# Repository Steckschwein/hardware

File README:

# Homebrew 8bit computer based on 65c02 CPU #

## Description ##
We are developing a retro style 8bit computer based on the 65c02 CPU. 

## Features ##
65c02 CPU @ 8MHz
TMS9929 Video Display Controller
Yamaha YM3812 (OPL2) Sound
rs232 serial interface using UART 16550
SD Card Interface

[Steckschwein Web Site](http://steckschwein.de/)

The goal is to design a machine that could have existed back in the home computer era, but with "modern" interfaces like PS/2, full fledged rs232, SPI, etc. 

We use as much open source tools as possible, such as 
ACME Cross Assembler
cc65
make
Mercurial
galasm
KiCAD
avr-gcc

The repository contains the assembler source for the system firmware, test and demo programs, galasm source for the address decoder and the KiCAD project files for schematics and layout.

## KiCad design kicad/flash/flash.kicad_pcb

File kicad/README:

the current steckschwein revision consists of three boards found in the directories
cpu_mem_rdy
io_uart
V9958_OPL2

everything else is kept for historical and sentimental reasons.

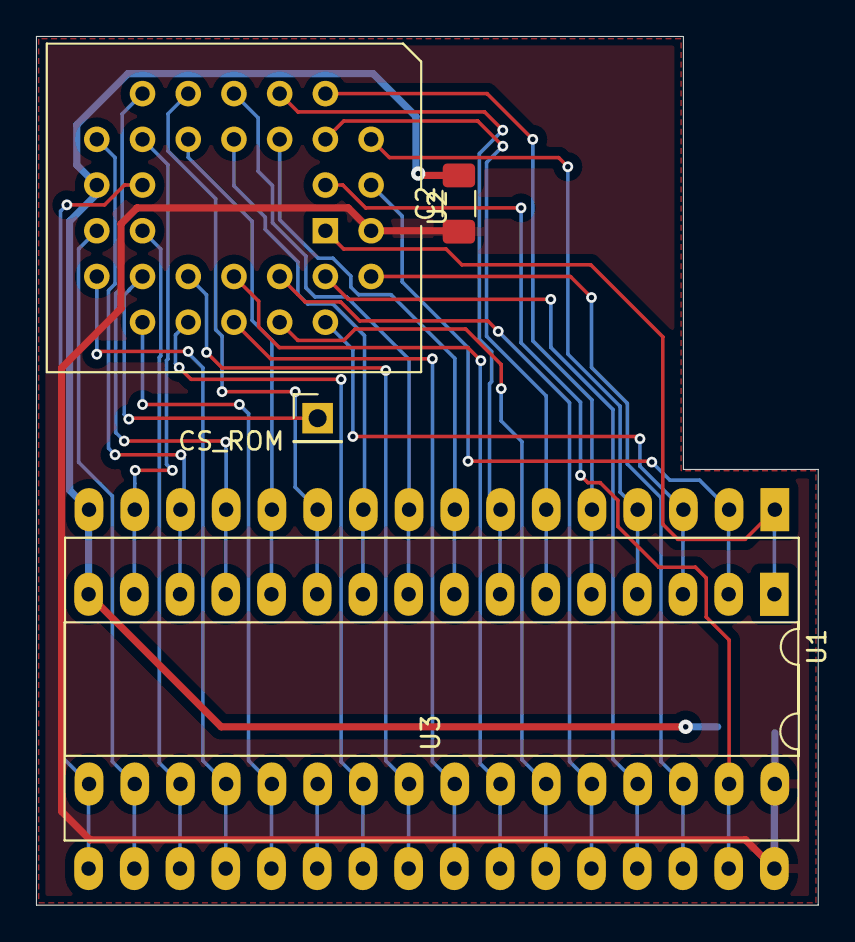
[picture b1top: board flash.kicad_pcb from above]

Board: 4 copper layers, 43.4 x 48.3 mm, 6 parts (1 on the bottom side), 33 nets.

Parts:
C1, C2: C; C_1206_3216Metric_Pad1.33x1.80mm_HandSolder
CS_ROM: Conn_01x01_Pin; PinHeader_1x01_P2.54mm_Vertical
U1, U3: AS6C4008-55PCN; DIP-32_W15.24mm_LongPads
U2: SST39SF040; PLCC-32_THT-Socket

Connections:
/A0: U1.12 (A0), U2.12 (A0), U3.12 (A0)
/A1: U1.11 (A1), U2.11 (A1), U3.11 (A1)
/A2: U1.10 (A2), U2.10 (A2), U3.10 (A2)
/A3: U1.9 (A3), U2.9 (A3), U3.9 (A3)
/A4: U1.8 (A4), U2.8 (A4), U3.8 (A4)
/A5: U1.7 (A5), U2.7 (A5), U3.7 (A5)
/A6: U1.6 (A6), U2.6 (A6), U3.6 (A6)
/A7: U1.5 (A7), U2.5 (A7), U3.5 (A7)
/A8: U1.27 (A8), U2.27 (A8), U3.27 (A8)
/A9: U1.26 (A9), U2.26 (A9), U3.26 (A9)
/A10: U1.23 (A10), U2.23 (A10), U3.23 (A10)
/A11: U1.25 (A11), U2.25 (A11), U3.25 (A11)
/A12: U1.4 (A12), U2.4 (A12), U3.4 (A12)
/A13: U1.28 (A13), U2.28 (A13), U3.28 (A13)
/A14: U1.3 (A14), U2.29 (A14), U3.3 (A14)
/A15: U1.31 (A15), U2.3 (A15), U3.31 (A15)
/A16: U1.2 (A16), U2.2 (A16), U3.2 (A16)
/A17: U1.30 (A17), U2.30 (A17), U3.30 (A17)
/A18: U1.1 (A18), U2.1 (A18), U3.1 (A18)
/D0: U1.13 (DQ0), U2.13 (D0), U3.13 (DQ0)
/D1: U1.14 (DQ1), U2.14 (D1), U3.14 (DQ1)
/D2: U1.15 (DQ2), U2.15 (D2), U3.15 (DQ2)
/D3: U1.17 (DQ3), U2.17 (D3), U3.17 (DQ3)
/D4: U1.18 (DQ4), U2.18 (D4), U3.18 (DQ4)
/D5: U1.19 (DQ5), U2.19 (D5), U3.19 (DQ5)
/D6: U1.20 (DQ6), U2.20 (D6), U3.20 (DQ6)
/D7: U1.21 (DQ7), U2.21 (D7), U3.21 (DQ7)
/~CE: U1.22 (CE#), U3.22 (CE#)
/~CS_ROM: CS_ROM.1, U2.22 (CE)
/~OE: U1.24 (OE#), U2.24 (OE), U3.24 (OE#)
/~WE: U1.29 (WE#), U2.31 (PGM), U3.29 (WE#)
GND: C1.2, C2.2, U1.16 (VSS), U2.16 (GND), U3.16 (VSS)
VCC: C1.1, C2.1, U1.32 (VCC), U2.32 (VCC), U3.32 (VCC)

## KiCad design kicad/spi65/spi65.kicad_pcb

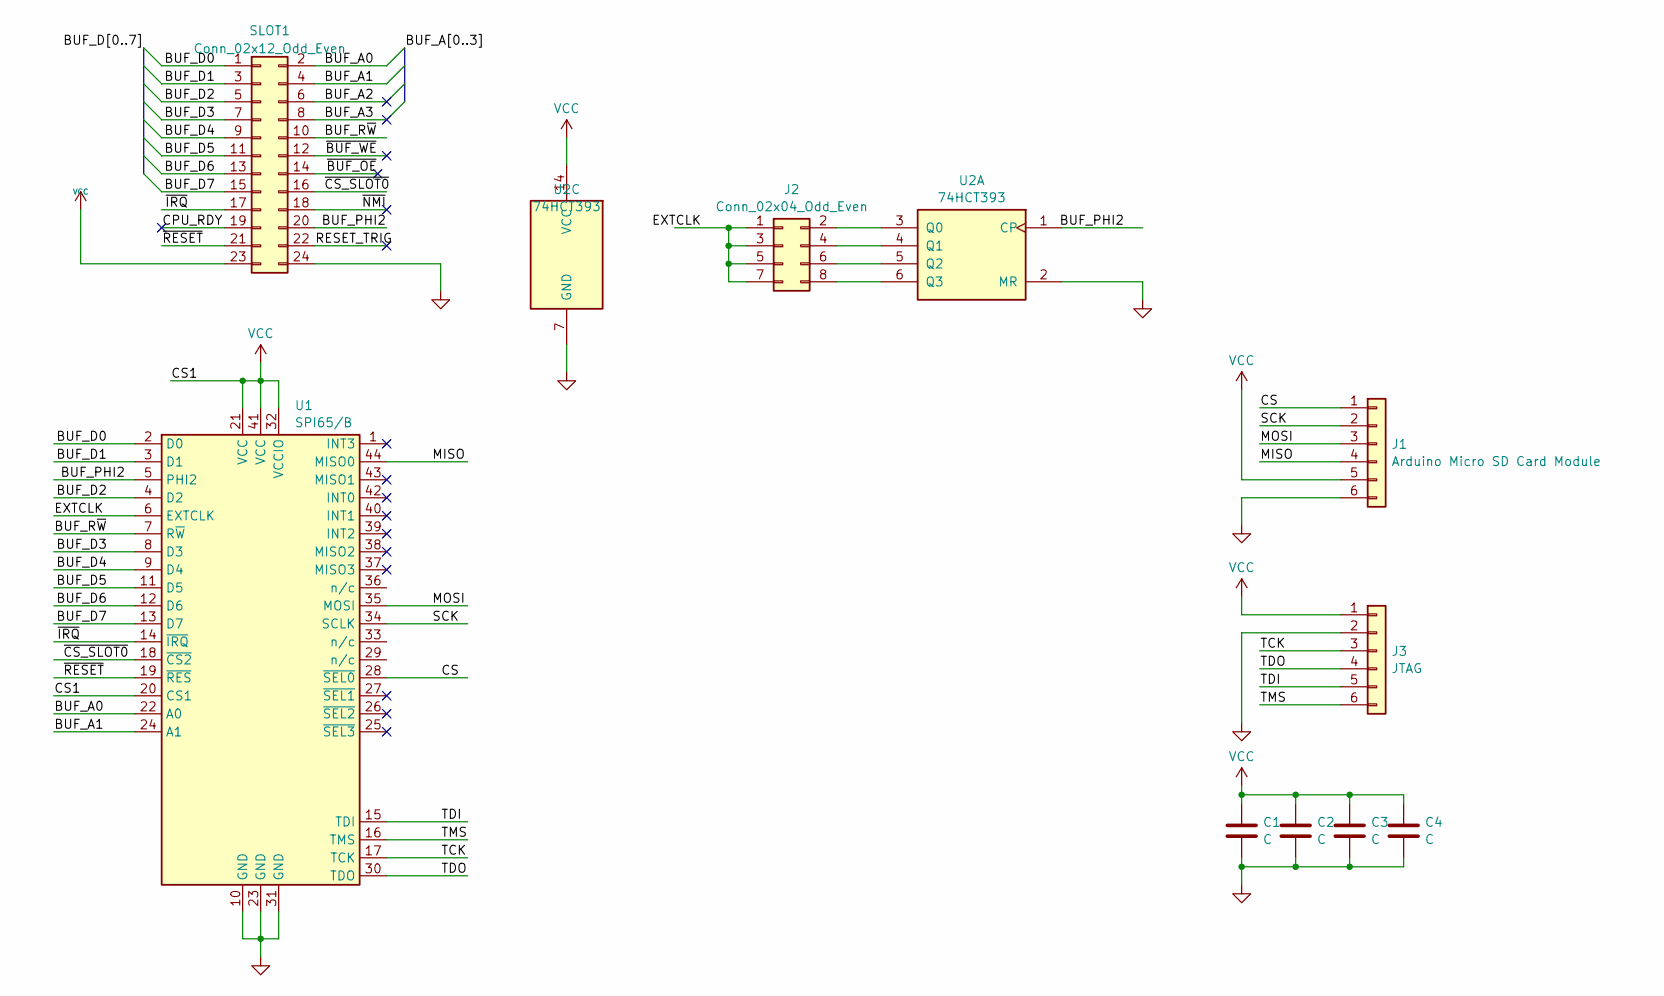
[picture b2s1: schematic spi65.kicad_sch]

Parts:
C1, C2, C3, C4: C; C_1206_3216Metric_Pad1.33x1.80mm_HandSolder
J1: Arduino Micro SD Card Module; MicroSD Card Adapter
J2: Conn_02x04_Odd_Even; PinHeader_2x04_P2.54mm_Vertical
J3: JTAG; PinHeader_1x06_P2.54mm_Vertical
SLOT1: Conn_02x12_Odd_Even; PinHeader_2x12_P2.54mm_Vertical
U1: SPI65/B; PLCC-44
U2: 74HCT393; DIP-14_W7.62mm_LongPads

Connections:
/BUF_A0: SLOT1.2, U1.22 (A0)
/BUF_A1: SLOT1.4, U1.24 (A1)
/BUF_A2: SLOT1.6
/BUF_A3: SLOT1.8
/BUF_D0: SLOT1.1, U1.2 (D0)
/BUF_D1: SLOT1.3, U1.3 (D1)
/BUF_D2: SLOT1.5, U1.4 (D2)
/BUF_D3: SLOT1.7, U1.8 (D3)
/BUF_D4: SLOT1.9, U1.9 (D4)
/BUF_D5: SLOT1.11, U1.11 (D5)
/BUF_D6: SLOT1.13, U1.12 (D6)
/BUF_D7: SLOT1.15, U1.13 (D7)
/BUF_PHI2: SLOT1.20, U1.5 (PHI2), U2.1 (CP)
/BUF_R~W: SLOT1.10, U1.7 (R~W)
/CPU_RDY: SLOT1.19
/CS: J1.1, U1.28 (~SEL0)
/EXTCLK: J2.1, J2.3, J2.5, J2.7, U1.6 (EXTCLK)
/MISO: J1.4, U1.44 (MISO0)
/MOSI: J1.3, U1.35 (MOSI)
/RESET_TRIG: SLOT1.22
/SCK: J1.2, U1.34 (SCLK)
/TCK: J3.3, U1.17 (TCK)
/TDI: J3.5, U1.15 (TDI)
/TDO: J3.4, U1.30 (TDO)
/TMS: J3.6, U1.16 (TMS)
/~BUF_OE: SLOT1.14
/~BUF_WE: SLOT1.12
/~CS_SLOT0: SLOT1.16, U1.18 (~CS2)
/~IRQ: SLOT1.17, U1.14 (~IRQ)
/~NMI: SLOT1.18
/~RESET: SLOT1.21, U1.19 (~RES)
GND: C1.2, C2.2, C3.2, C4.2, J1.6, J3.2, SLOT1.24, U1.10 (GND), U1.23 (GND), U1.31 (GND), U2.2 (MR), U2.7 (GND)
unnamed: J2.2, U2.3 (Q0)
unnamed: J2.4, U2.4 (Q1)
unnamed: J2.6, U2.5 (Q2)
unnamed: J2.8, U2.6 (Q3)
VCC: C1.1, C2.1, C3.1, C4.1, J1.5, J3.1, SLOT1.23, U1.20 (CS1), U1.21 (VCC), U1.32 (VCCIO), U1.41 (VCC), U2.14 (VCC)

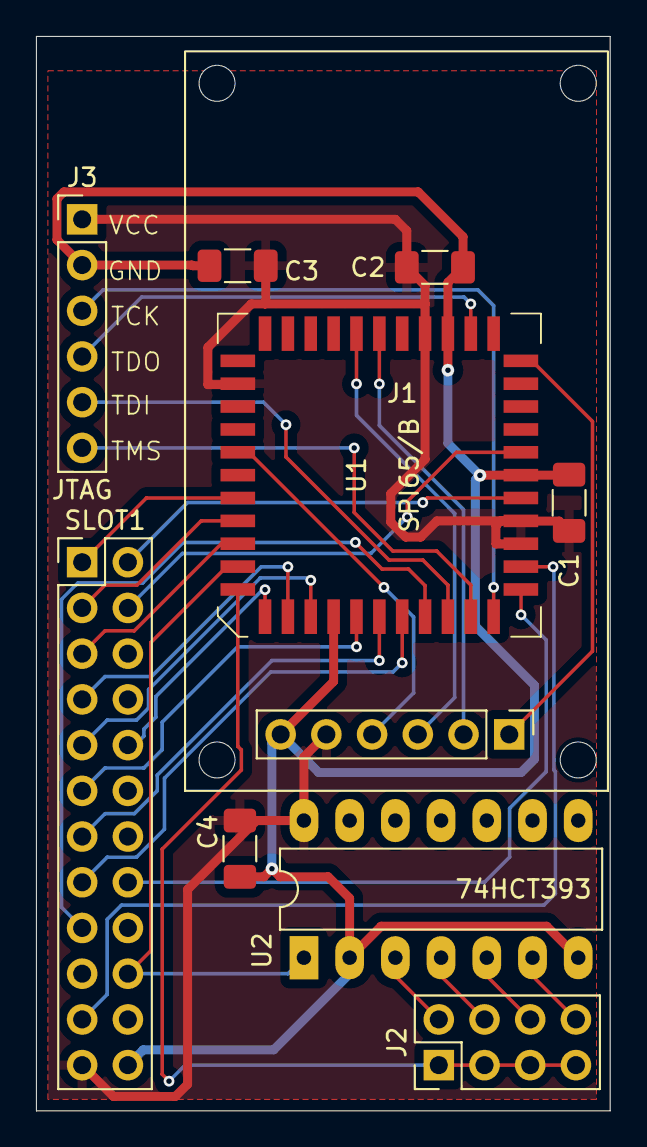
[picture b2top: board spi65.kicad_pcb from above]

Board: 2 copper layers, 31.9 x 59.7 mm, 10 parts (0 on the bottom side), 30 nets.

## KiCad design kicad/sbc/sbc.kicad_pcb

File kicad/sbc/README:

This directory contains the schematics of the CPU/memory-board with integrated RDY (wait state)-generator.
This is the current version of the CPU-Board

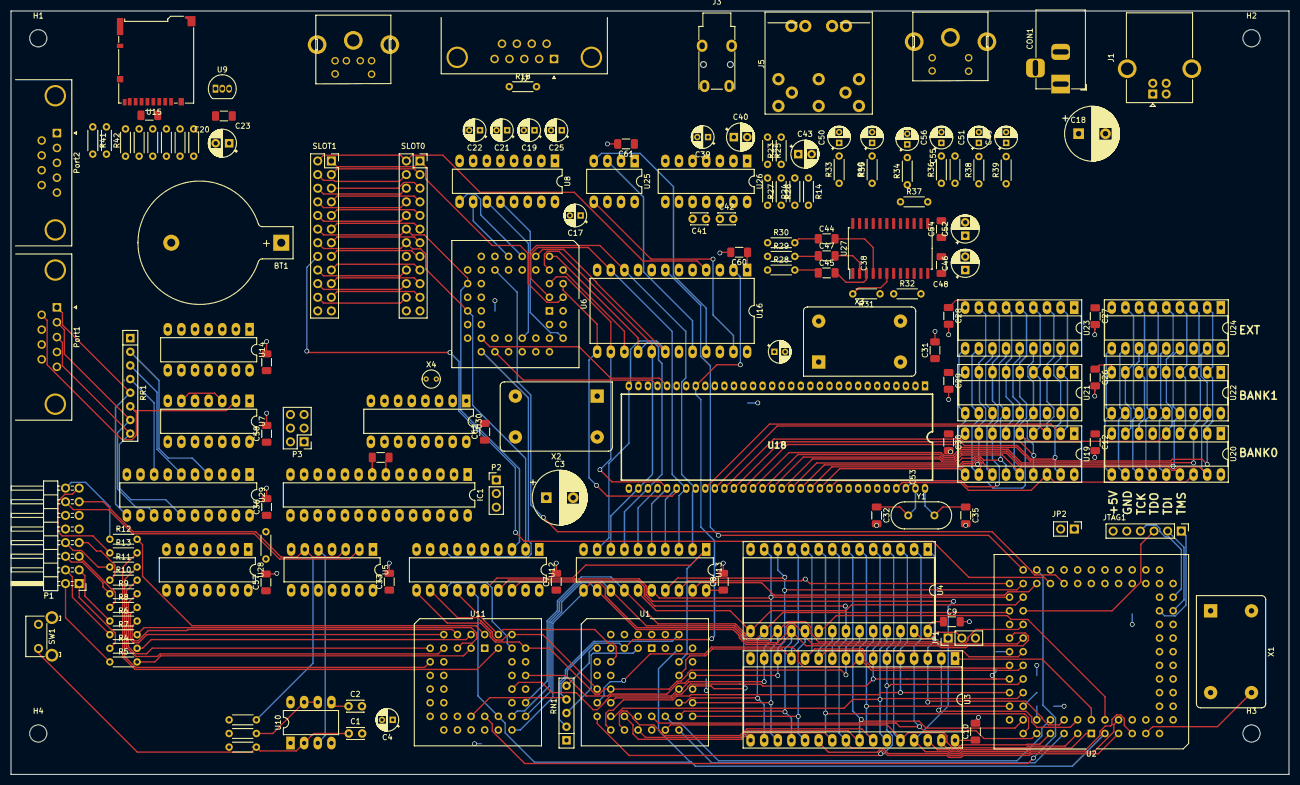
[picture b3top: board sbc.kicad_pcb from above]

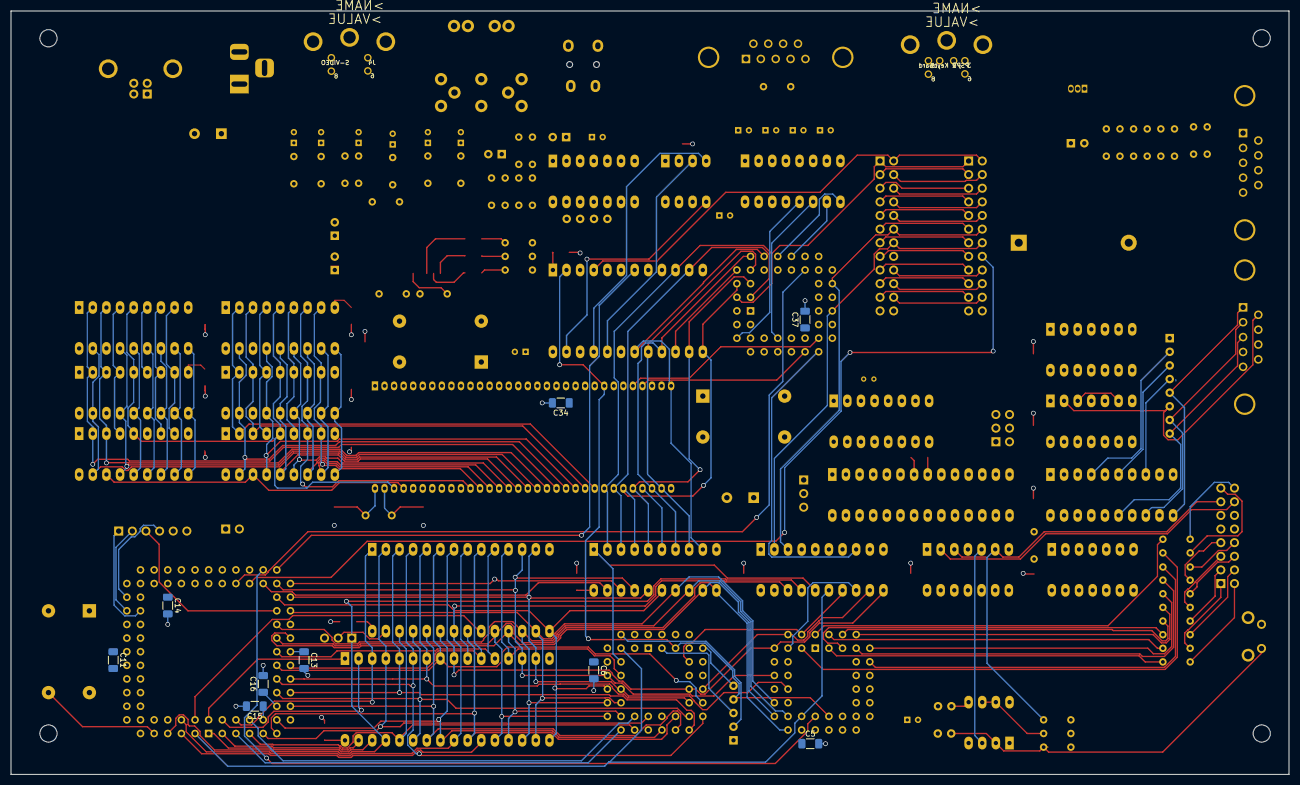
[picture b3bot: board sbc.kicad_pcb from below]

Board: 4 copper layers, 238.1 x 142.2 mm, 165 parts (9 on the bottom side), 221 nets.

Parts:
BT1: BATTERY; BatteryHolder_Keystone_103_1x20mm
C1: 10n; C_Disc_D3.0mm_W2.0mm_P2.50mm
C2: 1n; C_Disc_D3.0mm_W2.0mm_P2.50mm
C3, C18: 470µF; CP_Radial_D10.0mm_P5.00mm
C4: 1µ; CP_Radial_D4.0mm_P2.00mm
C5, C6, C7, C8, C9, C10, C11, C12, C13, C14, C26, C27, C28, C29, C30, C31, C33, C34, C36, C37, C44, C45, C47, C48, C54, C57, C58, C59, C60, C61, C62, C63: 100n; C_1206_3216Metric_Pad1.33x1.80mm_HandSolder
C15, C16, C23, C24: 100nF; C_1206_3216Metric_Pad1.33x1.80mm_HandSolder
C17, C19, C21, C22, C25: 1µF; CP_Radial_D4.0mm_P2.00mm
C20, C40, C43: 10µF; CP_Radial_D5.0mm_P2.50mm
C32, C35: 22p; C_1206_3216Metric_Pad1.33x1.80mm_HandSolder
C38: 100µF; CP_Radial_D4.0mm_P2.00mm
C39: 47µF; CP_Radial_D4.0mm_P2.00mm
C41, C42: 470p; C_Disc_D3.0mm_W2.0mm_P2.50mm
C46, C52: 47µF; CP_Radial_D5.0mm_P2.50mm
C49, C50, C51, C53, C55, C56: 220µF; CP_Radial_D4.0mm_P2.00mm
CON1: BARREL_JACK; BarrelJack_Horizontal
H1, H2, H3, H4: MountingHole_Pad; MountingHole_3.2mm_M3
IC1: ATMEGA8-P; DIP-28_W7.62mm_LongPads
J1: USB; USB_B_OST_USB-B1HSxx_Horizontal
J2: DB9; DSUB-9_Male_Horizontal_P2.77x2.84mm_EdgePinOffset4.94mm_Hou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
J3: AudioJack3; Jack_3.5mm_Lumberg_1503_07_Horizontal
J4: S-VIDEO; mini_din-M_DIN4
J5: RGB; DIN-8
JP1: Jumper_3_Bridged12; PinHeader_1x03_P2.54mm_Vertical
JP2: JUMPER; PinHeader_1x02_P2.54mm_Vertical
JTAG1: Conn_01x06_Male; PinHeader_1x06_P2.54mm_Vertical
P1: USERPORT; PinHeader_2x08_P2.54mm_Horizontal
P2: CONN_01X03; PinHeader_1x03_P2.54mm_Vertical
P3: ISP; PinHeader_2x03_P2.54mm_Vertical
P4: PS/2 Keyboard; mini_din-M_DIN6
Port1, Port2: DB9; DSUB-9_Male_Horizontal_P2.77x2.84mm_EdgePinOffset4.94mm_Hou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
R1, R2: 1M; R_Axial_DIN0204_L3.6mm_D1.6mm_P5.08mm_Horizontal
R3, R16: 4k7; R_Axial_DIN0204_L3.6mm_D1.6mm_P5.08mm_Horizontal
R4, R5, R6, R7, R8, R9, R10, R11, R12, R13, R15, R17, R41, R42: 1k; R_Axial_DIN0204_L3.6mm_D1.6mm_P5.08mm_Horizontal
R14, R24: 33K; R_Axial_DIN0204_L3.6mm_D1.6mm_P5.08mm_Horizontal
R18: 3k3; R_Axial_DIN0204_L3.6mm_D1.6mm_P5.08mm_Horizontal
R19, R20: 10k; R_Axial_DIN0204_L3.6mm_D1.6mm_P5.08mm_Horizontal
R21, R22: 47k; R_Axial_DIN0204_L3.6mm_D1.6mm_P5.08mm_Horizontal
R23, R27: 4K7; R_Axial_DIN0204_L3.6mm_D1.6mm_P5.08mm_Horizontal
R25: 15K; R_Axial_DIN0204_L3.6mm_D1.6mm_P5.08mm_Horizontal
R26: 27K; R_Axial_DIN0204_L3.6mm_D1.6mm_P5.08mm_Horizontal
R28, R29, R30: 470; R_Axial_DIN0204_L3.6mm_D1.6mm_P5.08mm_Horizontal
R31, R32: 2.2k; R_Axial_DIN0204_L3.6mm_D1.6mm_P5.08mm_Horizontal
R33, R34, R35, R38, R39: 75; R_Axial_DIN0204_L3.6mm_D1.6mm_P5.08mm_Horizontal
R36: 43; R_Axial_DIN0204_L3.6mm_D1.6mm_P5.08mm_Horizontal
R37: 2.61k/10%; R_Axial_DIN0204_L3.6mm_D1.6mm_P5.08mm_Horizontal
R40: 240; R_Axial_DIN0204_L3.6mm_D1.6mm_P5.08mm_Horizontal
RN1: 3k3; R_Array_SIP5
RR1: 1k; R_Array_SIP8
SLOT0, SLOT1: Conn_02x12_Odd_Even; PinSocket_2x12_P2.54mm_Vertical
SW1: SW_PUSH; SW_SPST_Omron_B3F-315x_Angled
U1: W65C02; PLCC-44_THT-Socket
U2: CHUCK; PLCC-84_THT-Socket
U3: AS6C4008; DIP-32_W15.24mm_Socket_LongPads
U4: 28C256; DIP-28_W15.24mm_Socket_LongPads
U5: 74LS06; DIP-14_W7.62mm_LongPads
U6: 16550; PLCC-44_THT-Socket
U7: 74125; DIP-14_W7.62mm_LongPads
U8: MAX232; DIP-16_W7.62mm_LongPads
U9: LP2950; TO-92_Inline
U10: LM555N; DIP-8_W7.62mm_LongPads
U11: W65C22NxPL; PLCC-44_THT-Socket
U12, U13: 74HCT245; DIP-20_W7.62mm_LongPads
U14: 7407; DIP-14_W7.62mm_LongPads
U15: Micro_SD_Card_Det1; microSD_HC_Hirose_DM3BT-DSF-PEJS
U16: YM3812; DIP-24_W15.24mm_LongPads
U18: V9958; SDIP64
U19, U20, U21, U22, U23, U24: DRAM_64KX4; DIP-18_W7.62mm_Socket_LongPads
U25: Y3014B; DIP-8_W7.62mm_LongPads
U26: LM324; DIP-14_W7.62mm_LongPads
U27: cxa2075M; SOIC-24W_7.5x15.4mm_P1.27mm
U28: 7400; DIP-14_W7.62mm_LongPads
U29: 74LS244; DIP-20_W7.62mm_LongPads
U30: DS1306; DIP-16_W7.62mm_LongPads
X1, X2, X3: OSC; Oscillator_DIP-14_LargePads
X4: CRYSTAL_SMD; Crystal_Round_D3.0mm_Vertical
Y1: 21,443Mhz; Crystal_HC49-U_Vertical

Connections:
/BUF_A0: SLOT0.2, SLOT1.2, U6.31 (A0), U12.6 (A4), U16.4 (A0), U18.29 (MODE0)
/BUF_A1: SLOT0.4, SLOT1.4, U6.30 (A1), U12.7 (A5), U18.28 (MODE1)
/BUF_A2: SLOT0.6, SLOT1.6, U6.29 (A2), U12.8 (A6)
/BUF_A3: SLOT0.8, SLOT1.8, U12.9 (A7)
/BUF_D0: SLOT0.1, SLOT1.1, U6.2 (D0), U13.2 (A0), U16.10 (D0), U18.40 (D0)
/BUF_D1: SLOT0.3, SLOT1.3, U6.3 (D1), U13.3 (A1), U16.11 (D1), U18.39 (D1)
/BUF_D2: SLOT0.5, SLOT1.5, U6.4 (D2), U13.4 (A2), U16.13 (D2), U18.38 (D2)
/BUF_D3: SLOT0.7, SLOT1.7, U6.5 (D3), U13.5 (A3), U16.14 (D3), U18.37 (D3)
/BUF_D4: SLOT0.9, SLOT1.9, U6.6 (D4), U13.6 (A4), U16.15 (D4), U18.36 (D4)
/BUF_D5: SLOT0.11, SLOT1.11, U6.7 (D5), U13.7 (A5), U16.16 (D5), U18.35 (D5)
/BUF_D6: SLOT0.13, SLOT1.13, U6.8 (D6), U13.8 (A6), U16.17 (D6), U18.34 (D6)
/BUF_D7: SLOT0.15, SLOT1.15, U6.9 (D7), U13.9 (A7), U16.18 (D7), U18.32 (D7)
/BUF_PHI2: SLOT0.20, SLOT1.20, U12.5 (A3)
/BUF_R~W: SLOT0.10, SLOT1.10, U12.4 (A2)
/CA1: P1.16, R12.1
/CA2: P1.15, R13.1
/CLKIN: U2.9 (I/O/GCK1), X1.8 (FREQ)
/CPU_A0: U1.10 (A0), U2.65, U3.12 (A0), U4.10 (A0), U11.42 (RS0), U12.14 (B4)
/CPU_A1: U1.11 (A1), U2.66, U3.11 (A1), U4.9 (A1), U11.41 (RS1), U12.13 (B5)
/CPU_A2: U1.13 (A2), U3.10 (A2), U4.8 (A2), U11.40 (RS2), U12.12 (B6)
/CPU_A3: U1.14 (A3), U3.9 (A3), U4.7 (A3), U11.39 (RS3), U12.11 (B7)
/CPU_A4: U1.15 (A4), U2.67, U3.8 (A4), U4.6 (A4)
/CPU_A5: U1.16 (A5), U2.68, U3.7 (A5), U4.5 (A5)
/CPU_A6: U1.17 (A6), U2.69, U3.6 (A6), U4.4 (A6)
/CPU_A7: U1.18 (A7), U2.70, U3.5 (A7), U4.3 (A7)
/CPU_A8: U1.19 (A8), U2.71, U3.27 (A8), U4.25 (A8)
/CPU_A9: U1.20 (A9), U2.72, U3.26 (A9), U4.24 (A9)
/CPU_A10: U1.21 (A10), U2.75, U3.23 (A10), U4.21 (A10)
/CPU_A11: U1.22 (A11), U2.76 (I/O/GTS1), U3.25 (A11), U4.23 (A11)
/CPU_A12: U1.25 (A12), U2.77 (I/O/GTS2), U3.4 (A12), U4.2 (A12)
/CPU_A13: U1.26 (A13), U2.79, U3.28 (A13), U4.26 (A13)
/CPU_A14: U1.27 (A14), U2.80
/CPU_A15: U1.28 (A15), U2.81
/CPU_D0: U1.36 (D0), U2.54, U3.13 (DQ0), U4.11 (D0), U11.36 (D0), U13.18 (B0)
/CPU_D1: U1.35 (D1), U2.55, U3.14 (DQ1), U4.12 (D1), U11.35 (D1), U13.17 (B1)
/CPU_D2: U1.34 (D2), U2.56, U3.15 (DQ2), U4.13 (D2), U11.34 (D2), U13.16 (B2)
/CPU_D3: U1.33 (D3), U2.57, U3.17 (DQ3), U4.15 (D3), U11.32 (D3), U13.15 (B3)
/CPU_D4: U1.32 (D4), U2.58, U3.18 (DQ4), U4.16 (D4), U11.31 (D4), U13.14 (B4)
/CPU_D5: U1.31 (D5), U2.61, U3.19 (DQ5), U4.17 (D5), U11.30 (D5), U13.13 (B5)
/CPU_D6: U1.30 (D6), U2.62, U3.20 (DQ6), U4.18 (D6), U11.29 (D6), U13.12 (B6)
/CPU_D7: U1.29 (D7), U2.63, U3.21 (DQ7), U4.19 (D7), U11.28 (D7), U13.11 (B7)
/CPU_RDY: JP2.1, RN1.3 (R2), SLOT0.19, SLOT1.19, U1.3 (RDY), U2.40
/CPU_R~W: U1.38 (R/~W), U11.24 (R/~W), U12.16 (B2), U13.1 (A->B)
/EXT_A14: U2.82, U3.3 (A14), U4.1 (A14)
/EXT_A15: U2.83, U3.31 (A15)
/EXT_A16: U2.84, U3.2 (A16)
/EXT_A17: U2.1, U3.30 (A17)
/EXT_A18: U2.2, U3.1 (A18)
/PA0: P1.1, R4.1, U29.9 (O0b), U29.18 (O0a)
/PA1: P1.2, R5.1, U29.7 (O1b), U29.16 (O1a)
/PA2: P1.3, R6.1, U29.5 (O2b), U29.14 (O2a)
/PA3: P1.4, R7.1, U29.3 (O3b), U29.12 (O3a)
/PA4: P1.5, R8.1, U7.3 (O), U7.6 (O)
/PA5: P1.6, R9.1
/PA6: P1.7, R10.1
/PA7: P1.8, R11.1, U28.1, U28.2, U28.4
/PHI2: U1.41 (ϕ0), U2.3, U11.27 (ϕ2), U12.15 (B3)
/RESET_TRIG: C1.1, IC1.23 ((ADC0)PC0), R1.2, SLOT0.22, SLOT1.22, SW1.1, U10.2 (TR)
/SD Card/CLK: R17.2, U14.8, U15.5 (CLK)
/SD Card/CMD: R19.2, U14.10, U15.3 (CMD)
/SD Card/DAT0: U7.9 (D), U15.7 (DAT0)
/SD Card/DAT1: R21.2, U15.8 (DAT1)
/SD Card/DAT2: R22.2, U15.1 (DAT2)
/SD Card/DAT3: R20.2, U14.12, U15.2 (DAT3/CD)
/SPI_CLK: IC1.19 ((SCK)PB5), P3.3, U11.10 (PB0), U11.19 (CB1), U14.9, U30.11 (SCLK)
/SPI_MISO: IC1.18 ((MISO)PB4), P3.1, U7.8 (O), U11.20 (CB2), U30.13 (SDO)
/SPI_MOSI: IC1.17 ((MOSI/OC2)PB3), P3.4, U11.18 (PB7), U14.11, U30.12 (SDI)
/TCK: JTAG1.4, U2.30 (TCK)
/TDI: JTAG1.2, U2.28 (TDI)
/TDO: JTAG1.3, U2.59 (TDO)
/TMS: JTAG1.1, U2.29 (TMS)
/Video_Audio/AD0: U18.49 (AD0), U19.14 (A0), U20.14 (A0), U21.14 (A0), U22.14 (A0), U23.14 (A0), U24.14 (A0)
/Video_Audio/AD1: U18.50 (AD1), U19.13 (A1), U20.13 (A1), U21.13 (A1), U22.13 (A1), U23.13 (A1), U24.13 (A1)
/Video_Audio/AD2: U18.51 (AD2), U19.12 (A2), U20.12 (A2), U21.12 (A2), U22.12 (A2), U23.12 (A2), U24.12 (A2)
/Video_Audio/AD3: U18.52 (AD3), U19.11 (A3), U20.11 (A3), U21.11 (A3), U22.11 (A3), U23.11 (A3), U24.11 (A3)
/Video_Audio/AD4: U18.53 (AD4), U19.8 (A4), U20.8 (A4), U21.8 (A4), U22.8 (A4), U23.8 (A4), U24.8 (A4)
/Video_Audio/AD5: U18.54 (AD5), U19.7 (A5), U20.7 (A5), U21.7 (A5), U22.7 (A5), U23.7 (A5), U24.7 (A5)
/Video_Audio/AD6: U18.55 (AD6), U19.6 (A6), U20.6 (A6), U21.6 (A6), U22.6 (A6), U23.6 (A6), U24.6 (A6)
/Video_Audio/AD7: U18.56 (AD7), U19.10 (A7), U20.10 (A7), U21.10 (A7), U22.10 (A7), U23.10 (A7), U24.10 (A7)
/Video_Audio/Audio_analog/AUDIO_OUT: C43.2, J3.R, J3.S, J5.1
/Video_Audio/Audio_analog/LOAD: U16.20 (SH), U25.3 (LOAD)
/Video_Audio/Audio_analog/SD: U16.21 (MO), U25.4 (SD)
/Video_Audio/Audio_analog/fl: U16.23 (fSY), U25.5 (fI)
/Video_Audio/CSYNC: R32.1, U18.6 (CSYNC)
/Video_Audio/OPL_CLK: U16.24 (fM), U18.8 (CPUCLK/VDS)
/Video_Audio/RD0: U18.41 (RD0), U19.2 (DQ0), U21.2 (DQ0), U23.2 (DQ0)
/Video_Audio/RD1: U18.42 (RD1), U19.3 (DQ1), U21.3 (DQ1), U23.3 (DQ1)
/Video_Audio/RD2: U18.43 (RD2), U19.15 (DQ2), U21.15 (DQ2), U23.15 (DQ2)
/Video_Audio/RD3: U18.44 (RD3), U19.17 (DQ3), U21.17 (DQ3), U23.17 (DQ3)
/Video_Audio/RD4: U18.45 (RD4), U20.2 (DQ0), U22.2 (DQ0), U24.2 (DQ0)
/Video_Audio/RD5: U18.46 (RD5), U20.3 (DQ1), U22.3 (DQ1), U24.3 (DQ1)
/Video_Audio/RD6: U18.47 (RD6), U20.15 (DQ2), U22.15 (DQ2), U24.15 (DQ2)
/Video_Audio/RD7: U18.48 (RD7), U20.17 (DQ3), U22.17 (DQ3), U24.17 (DQ3)
/Video_Audio/RGB_B: C44.1, R30.2, U18.24 (B)
/Video_Audio/RGB_G: C45.1, R28.2, U18.22 (G)
/Video_Audio/RGB_R: C47.1, R29.2, U18.23 (R)
/Video_Audio/VDP_R~W: U18.57 (R/W), U19.4 (WE), U20.4 (WE), U21.4 (WE), U22.4 (WE), U23.4 (WE), U24.4 (WE)
/Video_Audio/Video_analog/C_OUT: C49.2, J4.8
/Video_Audio/Video_analog/G_OUT: C53.2, J5.5
/Video_Audio/Video_analog/Y_OUT: C51.2, J4.6
/Video_Audio//CAS0: U18.61 (/CAS0), U19.16 (CAS), U20.16 (CAS)
/Video_Audio//CAS1: U18.60 (/CAS1), U21.16 (CAS), U22.16 (CAS)
/Video_Audio//CAS_X: U18.59 (/CAS_X), U23.16 (CAS), U24.16 (CAS)
/Video_Audio//RAS: U18.62 (/RAS), U19.5 (RAS), U20.5 (RAS), U21.5 (RAS), U22.5 (RAS), U23.5 (RAS), U24.5 (RAS)
/~BE: RN1.2 (R1), U1.40 (BE)
/~BUF_OE: SLOT0.14, SLOT1.14, U6.24 (~RD), U12.2 (A0)
/~BUF_WE: SLOT0.12, SLOT1.12, U6.20 (~WR), U12.3 (A1)
/~CSR_VDP: U2.47, U18.31 (/CSR)
/~CSW_VDP: U2.25, U18.30 (/CSW)
/~CS_BUFFER: U2.52, U13.19 (CE)
/~CS_OPL: U2.53, U16.7 (~CS)
/~CS_RAM: U2.5, U3.22 (CE#)
/~CS_ROM: U2.4, U4.20 (~CS)
/~CS_SLOT0: SLOT0.16, U2.39
/~CS_SLOT1: SLOT1.16, U2.50
/~CS_UART: U2.48, U6.16 (~CS2)
/~CS_VIA: U2.51, U11.25 (~CS2)
/~IRQ: IC1.25 ((ADC2)PC2), P1.14, RN1.4 (R3), SLOT0.17, SLOT1.17, U1.5 (~IRQ), U5.2, U11.23 (~IRQ), U16.2 (~IRQ), U18.25 (/INT), U30.5 (/INT0)
/~JOYPORT_ENABLE: U6.38 (~OUT1), U28.5, U28.9
/~NMI: IC1.24 ((ADC1)PC1), RN1.5 (R4), SLOT0.18, SLOT1.18, U1.7 (~NMI)
/~OE: U2.6, U3.24 (OE#), U4.22 (~OE), U12.18 (B0)
/~RESET: IC1.1 (PC6(~RESET)), P1.13, P3.5, R3.2, SLOT0.21, SLOT1.21, U1.44 (~RES), U2.74 (I/O/GSR), U5.3, U5.6, U11.37 (~RES), U16.3 (~IC), U18.9 (/RESET)
/~R: U2.26, U16.6 (~RD)
/~SD_CARD_DETECT: R15.1, U15.9 (DET)
/~SPI_SS1: IC1.16 ((~SS/OC1B)PB2), U7.10 (EN), U11.12 (PB1), U14.13, U28.12, U28.13
/~WE: JP1.1 (A), U2.7, U3.29 (WE#), U12.17 (B1)
/~W: U2.11, U16.5 (~WR)
GND: BT1.2, C1.2, C2.2, C3.2, C4.2, C5.2, C6.2, C7.2, C8.2, C9.2, C10.2, C11.2, C12.2, C13.2, C14.2, C15.2, C16.2, C17.2, C18.2, C20.2, C22.1, C23.2, C24.2, C26.2, C27.2, C28.2, C29.2, C30.2, C31.2, C32.2, C33.2, C34.2, C35.2, C36.2, C37.2, C38.2, C39.2, C40.2, C41.1, C46.2, C48.2, C52.2, C54.2, C57.2, C58.2, C59.2, C60.2, C61.2, C62.2, C63.2, CON1.2, IC1.8 (GND), IC1.22 (AGND), J1.4 (GND), J2.5, J3.T, J4.3, J4.5, J4.SH1 (PE1), J4.SH2 (PE2), J4.SH3 (PE3), J5.2, JTAG1.5, P1.9, P2.1, P3.6, P4.3, P4.SH1 (PE1), P4.SH2 (PE2), P4.SH3 (PE3), Port1.8, Port2.8, R23.1, R27.1, R28.1, R29.1, R30.1, R40.2, SLOT0.24, SLOT1.24, SW1.2, U1.1 (VSS), U1.23 (VSS), U1.24 (VSS), U2.8 (GND), U2.16 (GND), U2.27 (GND), U2.42 (GND), U2.49 (GND), U2.60 (GND), U3.16 (VSS), U4.14 (GND), U5.7 (GND), U5.9, U5.11, U5.13, U6.21 (WR), U6.22 (GND), U6.25 (RD), U6.28 (~ADS), U7.7 (GND), U7.12 (D), U8.15 (GND), U9.2 (GND), U10.1 (GND), U11.1 (VSS), U12.1 (A->B), U12.10 (GND), U12.19 (CE), U13.10 (GND), U14.1, U14.3, U14.5, U14.7 (Gnd), U15.4 (VDD), U15.10 (SHIELD), U16.12 (GND), U18.1 (GND), U18.20 (GND/DAC), U19.1 (OE), U19.18 (VSS), U20.1 (OE), U20.18 (VSS), U21.1 (OE), U21.18 (VSS), U22.1 (OE), U22.18 (VSS), U23.1 (OE), U23.18 (VSS), U24.1 (OE), U24.18 (VSS), U25.6 (GND), U26.11 (V-), U27.1 (GND1), U27.7 (NPIN), U27.24 (GND2), U28.7 (GND), U29.10 (GND), U30.1 (VCC2), U30.8 (GND), X1.7 (GND), X2.7 (GND), X3.7 (GND)
unnamed: C42.2, R14.2, R24.1
unnamed: C43.1, R26.2, R27.2, U26.14
unnamed: C49.1, R39.2
unnamed: C50.1, R33.2
unnamed: C50.2, J5.6
unnamed: C51.1, R38.2
unnamed: C53.1, R34.2
unnamed: C55.1, R35.2
unnamed: C55.2, J5.8
unnamed: C56.1, R36.2, R40.1
unnamed: C56.2, J5.3, J5.7
unnamed: IC1.12 ((AIN0)PD6), P4.1
unnamed: IC1.13 ((AIN1)PD7), P4.2
unnamed: IC1.4 ((INT0)PD2), P4.6
unnamed: IC1.5 ((INT1)PD3), P4.8
unnamed: IC1.2 ((RXD)PD0), P2.2
unnamed: IC1.3 ((TXD)PD1), P2.3
unnamed: J2.4, R18.1
unnamed: JP1.2 (C), U4.27 (~WE)
unnamed: Port1.6, RR1.6, U7.2 (D)
unnamed: Port2.6, R42.1, U7.5 (D)
unnamed: U5.1, U6.33 (INTR)
unnamed: R16.2, U5.4, U6.39 (MR)
unnamed: U6.10 (RCLK), U6.17 (~BAUDOUT)
unnamed: U6.11 (SIN), U8.9 (R2OUT)
unnamed: U6.13 (SOUT), U8.10 (T2IN)
unnamed: U6.18 (XIN), X2.8 (FREQ)
unnamed: U6.40 (~CTS), U8.12 (R1OUT)
unnamed: U6.36 (~RTS), U8.11 (T1IN)
unnamed: C19.1, U8.1 (C1+)
unnamed: C19.2, U8.3 (C1-)
unnamed: C21.1, U8.4 (C2+)
unnamed: C21.2, U8.5 (C2-)
unnamed: J2.8, U8.13 (R1IN)
unnamed: J2.2, U8.8 (R2IN)
unnamed: J2.7, U8.14 (T1OUT)
unnamed: J2.3, U8.7 (T2OUT)
unnamed: C25.2, R18.2, U8.2 (VS+)
unnamed: C22.2, U8.6 (VS-)
unnamed: C2.1, U10.5 (CV)
unnamed: C4.1, R2.1, U10.6 (THR), U10.7 (DIS)
unnamed: U5.5, U10.3 (Q)
unnamed: R12.2, U11.44 (CA1)
unnamed: R13.2, U11.43 (CA2)
unnamed: R4.2, U11.2 (PA0)
unnamed: R5.2, U11.3 (PA1)
unnamed: R6.2, U11.4 (PA2)
unnamed: R7.2, U11.5 (PA3)
unnamed: R8.2, U11.6 (PA4)
unnamed: R9.2, U11.7 (PA5)
unnamed: R10.2, U11.8 (PA6)
unnamed: R11.2, U11.9 (PA7)
unnamed: R15.2, U11.17 (PB6)
unnamed: C20.1, C24.1, R17.1, R19.1, R20.1, R21.1, R22.1, U9.1 (VO), U15.6 (VSS)
unnamed: C32.1, U18.63 (XTAL1), Y1.1
unnamed: C35.1, U18.64 (XTAL2), Y1.2
unnamed: JP2.2, U18.26 (/WAIT)
unnamed: R23.2, R25.1, U25.8 (MP), U26.6 (-), U26.7
unnamed: C40.1, U25.7 (RB), U26.5 (+)
unnamed: U25.2 (ToBUFF), U26.3 (+)
unnamed: R14.1, U26.1, U26.2 (-)
unnamed: C41.2, R24.2, U26.10 (+)
unnamed: C42.1, U26.8, U26.9 (-), U26.12 (+)
unnamed: R25.2, R26.1, U26.13 (-)
unnamed: C44.2, U27.4 (BIN)
unnamed: R35.1, U27.21 (BOUT)
unnamed: R39.1, U27.15 (COUT)
unnamed: R36.1, U27.20 (CVOUT)
unnamed: C45.2, U27.3 (GIN)
unnamed: R34.1, U27.22 (GOUT)
unnamed: C47.2, U27.2 (RIN)
unnamed: R33.1, U27.23 (ROUT)
unnamed: R31.2, U27.6 (SCIN)
unnamed: R32.2, U27.10 (SYNCIN)
unnamed: R38.1, U27.16 (YOUT)
unnamed: R37.1, U27.17 (YTRAP)
unnamed: U28.3, U28.10
unnamed: Port2.1, R41.1, U29.2 (I0a)
unnamed: Port1.1, RR1.5, U29.11 (I0b)
unnamed: Port2.2, RR1.2, U29.4 (I1a)
unnamed: Port1.2, RR1.7, U29.13 (I1b)
unnamed: Port2.3, RR1.3, U29.6 (I2a)
unnamed: Port1.3, RR1.8, U29.15 (I2b)
unnamed: Port2.4, RR1.4, U29.8 (I3a)
unnamed: Port1.4, U29.17 (I3b)
unnamed: U7.4 (EN), U28.8, U29.1 (OEa)
unnamed: U7.1 (EN), U28.6, U29.19 (OEb)
unnamed: U28.11, U30.10 (CE)
unnamed: BT1.1, U30.2 (VBAT)
unnamed: U30.3 (X1), X4.2
unnamed: U30.4 (X2), X4.1
unnamed: R31.1, X3.8 (FREQ)
VCC: C3.1, C5.1, C6.1, C7.1, C8.1, C9.1, C10.1, C11.1, C12.1, C13.1, C14.1, C15.1, C16.1, C17.1, C18.1, C23.1, C25.1, C26.1, C27.1, C28.1, C29.1, C30.1, C31.1, C33.1, C34.1, C36.1, C37.1, C38.1, C39.1, C46.1, C48.1, C52.1, C54.1, C57.1, C58.1, C59.1, C60.1, C61.1, C62.1, C63.1, CON1.1, IC1.7 (VCC), IC1.20 (AVCC), IC1.21 (AREF), J1.1 (VBUS), J5.4, JP1.3 (B), JTAG1.6, P1.10, P3.2, P4.5, Port1.7, Port2.7, R1.1, R2.2, R3.1, R16.1, R37.2, R41.2, R42.2, RN1.1 (common), RR1.1 (COM), SLOT0.23, SLOT1.23, U1.9 (VDD), U1.37 (VDD), U2.22 (VCCIO), U2.38 (VCC), U2.64 (VCCIO), U2.73 (VCC), U2.78 (VCC), U3.32 (VCC), U4.28 (VCC), U5.14 (VCC), U6.14 (CS0), U6.15 (CS1), U6.41 (~DSR), U6.42 (~DCD), U6.43 (~RI), U6.44 (VCC), U7.13 (EN), U7.14 (VCC), U8.16 (VCC), U9.3 (VI), U10.4 (R), U10.8 (VCC), U11.21 (VDD), U11.26 (CS1), U12.20 (VCC), U13.20 (VCC), U14.14 (Vcc), U16.1 (VCC), U18.4 (VRESET), U18.21 (VCC/DAC), U18.27 (/HRESET), U18.58 (VCC), U19.9 (VCC), U20.9 (VCC), U21.9 (VCC), U22.9 (VCC), U23.9 (VCC), U24.9 (VCC), U25.1 (VCC), U26.4 (V+), U27.12 (VCC1), U27.19 (VCC2), U28.14 (VCC), U29.20 (VCC), U30.9 (MODE), U30.14 (VCCIF), U30.16 (VCC1), X1.14 (+5V), X2.14 (+5V), X3.14 (+5V)

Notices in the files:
kicad/cpu_mem_cpld/cpu_mem_cpld.kicad_pcb:
(C) 2022 Woinke / Lauke
kicad/sbc/sbc.kicad_pcb:
(c) 2023 Thomas Woinke / Marko Lauke
